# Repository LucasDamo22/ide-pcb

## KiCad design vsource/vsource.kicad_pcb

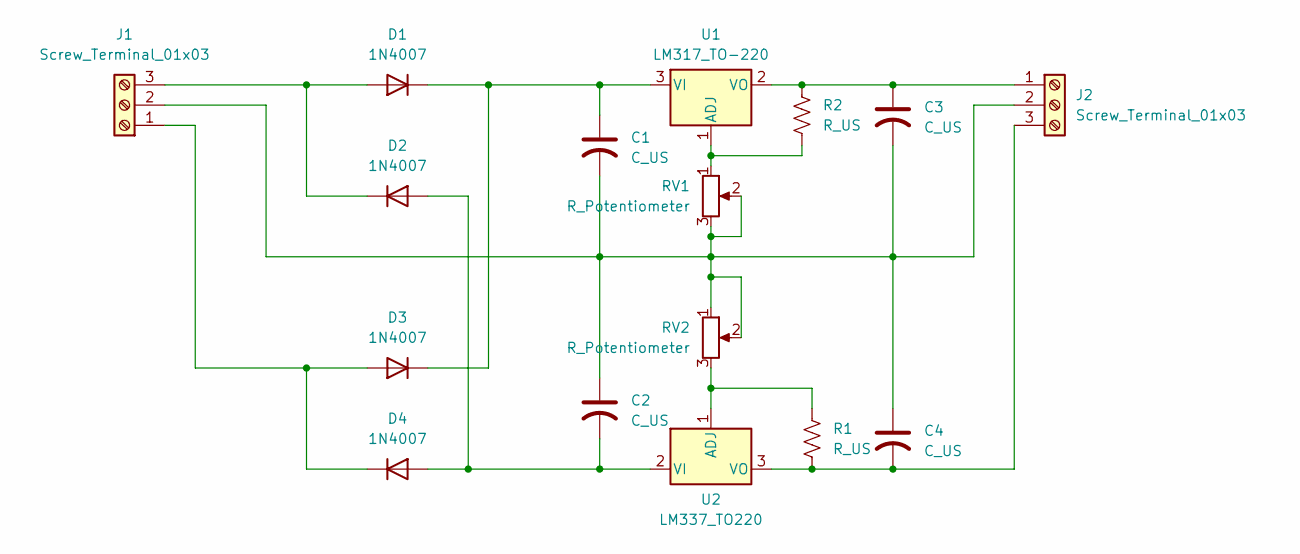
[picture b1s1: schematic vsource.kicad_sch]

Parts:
C1, C2: C_US; CP_Radial_D16.0mm_P7.50mm
C3, C4: C_US; CP_Radial_D5.0mm_P2.50mm
D1, D2, D3, D4: 1N4007; D_DO-41_SOD81_P10.16mm_Horizontal
J1, J2: Screw_Terminal_01x03; Altech_AK100_1x03_P5.00mm
R1, R2: R_US; R_Axial_DIN0204_L3.6mm_D1.6mm_P7.62mm_Horizontal
RV1, RV2: R_Potentiometer; Potentiometer_Alps_RK09Y11_Single_Horizontal
U1: LM317_TO-220; TO-220-3_Vertical
U2: LM337_TO220; TO-220-3_Vertical

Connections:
unnamed: D1.2 (A), D2.1 (K), J1.3
unnamed: C1.1, D1.1 (K), D3.1 (K), U1.3 (VI)
unnamed: C2.2, D2.2 (A), D4.2 (A), U2.2 (VI)
unnamed: D3.2 (A), D4.1 (K), J1.1
unnamed: C1.2, C2.1, C3.2, C4.1, J1.2, J2.2, RV1.2, RV1.3, RV2.1, RV2.2
unnamed: C3.1, J2.1, R2.1, U1.2 (VO)
unnamed: C4.2, J2.3, R1.1, U2.3 (VO)
unnamed: R2.2, RV1.1, U1.1 (ADJ)
unnamed: R1.2, RV2.3, U2.1 (ADJ)

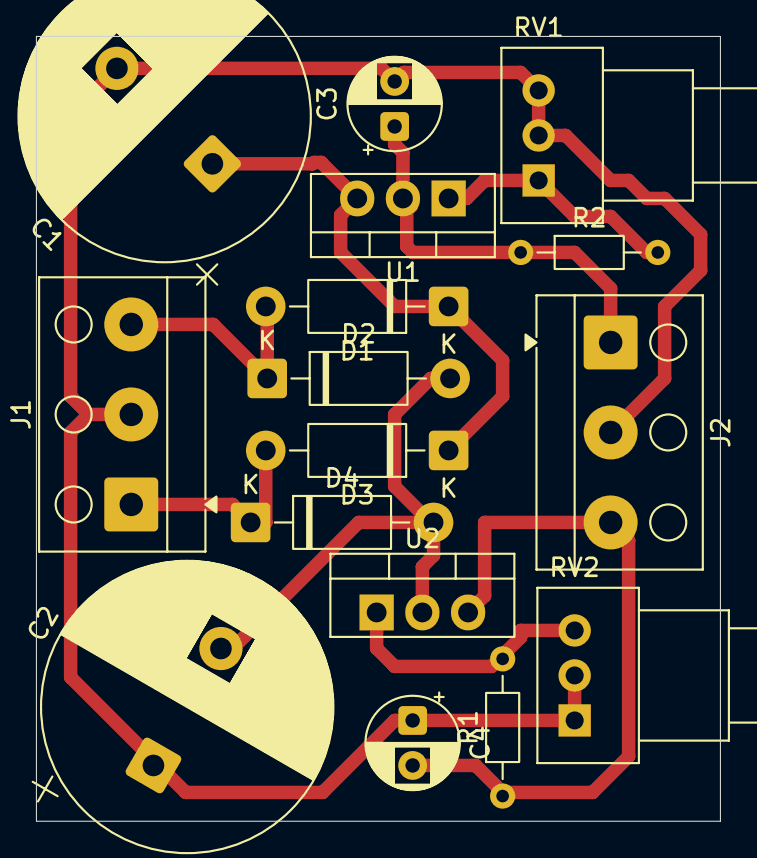
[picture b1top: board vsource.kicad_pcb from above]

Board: 2 copper layers, 38.0 x 43.6 mm, 16 parts (0 on the bottom side), 9 nets.
